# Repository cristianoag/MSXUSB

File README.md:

# MSX-USB
## Some history
In the 80's the MSX standard was created by Kazuhiko Nishi. He envisioned a simple yet powerful home computer based on standard hardware, software (BIOS/MSX DOS) and connectivity. From 1983 to 1990 manufacturers, like Philips, Sony, Yamaha, Sharp, Canon and many more, made computers according to this standard.

Because of the fact that extensibility was part of the standard people could design cartridges that would add synthesizer sound, memory, modems, rom-based games, or combinations of the above.

Cartridges were connected via a standard 50pin connector that remained the same accross 4 generations of MSX (1/2/2+/TurboR). BIOS and MSX-DOS were designed in a way to discover these via rom-based drivers, software hooks, extended bios.

Standardisation offers a big advantage because everything that adheres to the standard can connect to it.

## USB
USB was designed in the 90's to do something similar. To standardize the connection of peripherals to personal computers, both to communicate with and to supply electric power. It has now largely replaced interfaces such as serial ports and parallel ports, and has become commonplace on a wide range of devices. Like USB flash drives, keyboards, mice, wifi, serial, camera's, etc.

What if the MSX would have an USB connection? And if the BIOS/MSX DOS would automatically recognize devices connected to it?

## Meet MSX-USB
Inspired by the work of Xavirompe and his [RookieDrive](http://rookiedrive.com/en/) S0urceror set out to do build an open source project that would add USB to the MSX. The project is called MSX-USB and is hosted on GitHub. 

The project had contributions of many people in the MSX community. With people contributing to improve the hardware, firmware, drivers, and documentation.

On this GitHub page you can find:
* Schematics (KiCAD), that interfaces a cheap USB CH376s board to the MSX cartridge port.
* Drivers, currently Flash drives on Nextor and HID keyboards are supported.
* Debugging tools, to connect a test board to your PC/MAC and assist in debugging.

## Hardware

This project connects the CH376s board you can find on eBay or AliExpress for around 4 USD to the MSX.  The CH376s board is a USB host controller that can handle USB devices. The board is connected to the MSX cartridge port and is controlled by a CPLD. The CPLD is programmed to handle the MSX bus protocol and to interface with the CH376s board.

Circuitry is added to correctly handle the _BUSDIR signal. Make sure you select parallel by setting the jumper on the CH376s board correctly.

The CH376s board is accessible via ports 10h and 11h on the MSX, where port 11h serves as the command port and port 10h as the data port. 

Programming details for the CH376s can be found in various online resources:
* [CH376s Datasheet](https://www.mpja.com/download/ch376ds1.pdf)
* [Arduino Basics: CH376s USB Read/Write Module](https://arduinobasics.blogspot.com/2015/05/ch376s-usb-readwrite-module.html)

Most information is available on how to use the higher-order API for flash drives. 

If you want to use other USB devices you have to go low-level. As it turns out Konamiman already did some work there and after some researching I got USB HID Keyboards, Ethernet, Serial working as well. Check out my source-code or these great pages for more information:

* http://www.usbmadesimple.co.uk/index.html
* https://www.beyondlogic.org/usbnutshell/usb1.shtml

### PCB

If you prefer using PLCC versions of the CPLD and flash memory chips, it is recommended to use the v4 PCB by @cristianoag. This version fits into a Konami-style cartridge case and includes a switch to toggle between two ROM images. Be sure to use the rev4 CPLD code to enable this functionality. You can find the Gerber files and CPLD code for v4 at these links: [Gerber Files](hardware/v4/kicad-cpld-rev4/production) and [CPLD Code](hardware/v4/quartus-rev4).

If you’re comfortable with SMD soldering and want to avoid the challenges of sourcing 7064SLC without JTAG locks, use the v5 CPLD code and PCBs instead (also created by @cristianoag). The files for these are available at: [CPLD Code](hardware/v5/cpld) and [PCB Files](hardware/v5/kicad). The v5 CPLD verilog code also includes support to the additional 20h and 21h ports so enabling the use of new drivers that were developed for those ports by Konamiman.

Please note that for v5 there are two folders for the PCBs because there are different types of CH376 modules available. Depending on the module you have, you’ll need to use a specific version of the PCB. Compare the signals of your module with those on the PCBs to ensure you select the correct one.

**Very important:** The MSX-USB project requires modules with the CH376S firmware with at least version 0x43 (Version 3). If you have a CH376 module with a CH376S chip with versions 0x41 or 0x42 the drivers will not work. You can check the version of the firmware by issuing a CMD_GET_IC_VER command to the CH376S chip. Also some of the drivers display the version of the CH376S firmware when they are loaded.

## BIOS and Drivers

The project has several bios and drivers that have been developed. You can use a flash programmer or the MSX itself to flash the bios options to the flash chip on the cartridge. To do that use the flash.com tool that is available in the software folder. 

The flash.com command has the following syntax:

```
flash.com <filename>.rom
```

The [flash.com tool](software/flash/dist/flash.com) supports AMC_A29040B (AMIC A29040B), AMD_AM29F040, AMD_AM29F010 and SST_SST39SF040 chips. It detects the chip and selects the appropriate identification, erase and programming commands. Other chips require an external flash programmer.

Use `flash.com /S1 <filename>.rom` (or `/S0`, `/S2`, `/S3`) to select a primary slot instead of scanning all four slots. The selected slot is still checked for a supported chip before erasing. The tool erases the entire flash chip, not just the space occupied by the ROM file.

SST39SF040 commands use flash addresses `0x5555` and `0x2AAA`, rather than the shorter AMD/AMIC unlock addresses. The tool maps dedicated 8 KB command banks and temporarily replaces page 2 RAM while issuing SST commands, restoring RAM before accessing the file buffer or DOS. SST detection requires the stack to be in page 3, with at least 256 bytes available above `0xC000`. This requires the MSX-USB mapper's `5x00`/`7x00`/`9x00` bank-register decoding, as implemented by the v3, v4 and v5 CPLD sources. On v4, select the first ROM bank with the hardware switch so flash address zero is accessible for SST identification.

The host-side flash regression tests can be run with `make -C software/flash test` (Node.js and a C++17 `g++` compiler are required; `CXX` can select another compatible compiler). They exercise the actual C protocol and command-line code against a simulated flash chip and cartridge mapper; they do not replace testing on physical hardware. SST command and polling behavior follows the [Microchip datasheet](https://ww1.microchip.com/downloads/aemDocuments/documents/MPD/ProductDocuments/DataSheets/SST39SF010A-SST39SF020A-SST39SF040-Data-Sheet-DS20005022.pdf).

### USB Host BIOS (USBHOST.ROM)

S0urceror wrote a UNAPI USB specification and implemented the Usb Host driver according to it. The next version of this Host driver will also implement the Usb Hub specification and enumerate and initialise all devices connected.

* **USB HID Keyboard Driver** The Usb Keyboard driver is a program that connects to Unapi Usb driver and hooks itself to H.CHGE. From that moment on it replaces your trusted MSX keyboard by a shiny new USB Keyboard. Or a wireless one if you have inserted the appropriate Logitech receiver.

* **USB CDC ECM Ethernet Driver** The USB CDC ECM Ethernet driver is finished. It uses the Unapi USB and conforms to the Unapi Ethernet standard. Internestor Lite can now connect and use your USB Ethernet device. Please note that currently we only support USB CDC ECM. Make sure your Ethernet device supports this. All USB Ethernet devices built around the **RTL8153** chipset support USB CDC ECM. They usually cost around 20 euro.

### USB Storage NEXT (USBNEXT.ROM)

This is a firmware developed in C that implements a menu that is capable to mount DSK files or boot the computer from a connected USB stick. It also is a Nextor driver that allows you to use the USB stick as a hard disk. 

You can choose between (1) to initialize via floppy disk, (2) to initialize via USB stick, or use letters correspondent to files and folders located on the root of the USB stick connected to the cartridge to navigate and mount DSK files.

This BIOS allows mounting DSK files that are bigger than 720KB, respecting the limitations imposed by the Nextor OS.

### Konamiman USB FDD Firmware (USBFDD.ROM)

Konamiman developed a BIOS that allows you to mount DSK 360K/720K images stored on a USB floppy drive and use them as if they were real floppy disks. This version also allows you to boot the computer from a connected USB floppy drive compatible with the UFI standard.

You can check the [Konamiman's Floppy Disk Controller ROM](https://github.com/Konamiman/RookieDrive-FDD-ROM) GitHub repository for more information. He also provides a full manual page describing how to use the BIOS in the [Disk Image Mode](https://github.com/Konamiman/RookieDrive-FDD-ROM/blob/master/DISK_IMAGE_MODE.md).

@cristianoag adapted the original BIOS to work with the MSX-USB project. You can find the adapted version in the [MsxUSBFDD](/drivers/MsxUSBFDD) folder. 

## Installation instructions
Check [this page](INSTALL.md) for installation instructions and links to the various binaries that have been developed.

## Build your own (DIY)
Check [this page](DIY.md) for information on how to make the PCB, program the CPLD device, flash the ROM, etc.

## Collaboration
Interested in contributing to the MSX-USB project? Whether you want to develop drivers for additional devices or assist in other areas, your help is welcome. Clone the repository and start contributing by filing issues, submitting pull requests, or sharing your ideas.

## License

This work is licensed under a [Creative Commons Attribution-NonCommercial-ShareAlike 4.0 International License](http://creativecommons.org/licenses/by-nc-sa/4.0/).

* If you remix, transform, or build upon the material, you must distribute your contributions under the same license as the original.
* You may not use the material for commercial purposes.
* You must give appropriate credit, provide a link to the license, and indicate if changes were made. You may do so in any reasonable manner, but not in any way that suggests the licensor endorses you or your use.

**ATTENTION**

This project was made for the retro community and not for commercial purposes. So only retro hardware forums and individual people can build this project.

THE SALE OF ANY PART OF THIS PROJECT WITHOUT EXPRESS AUTHORIZATION IS PROHIBITED!

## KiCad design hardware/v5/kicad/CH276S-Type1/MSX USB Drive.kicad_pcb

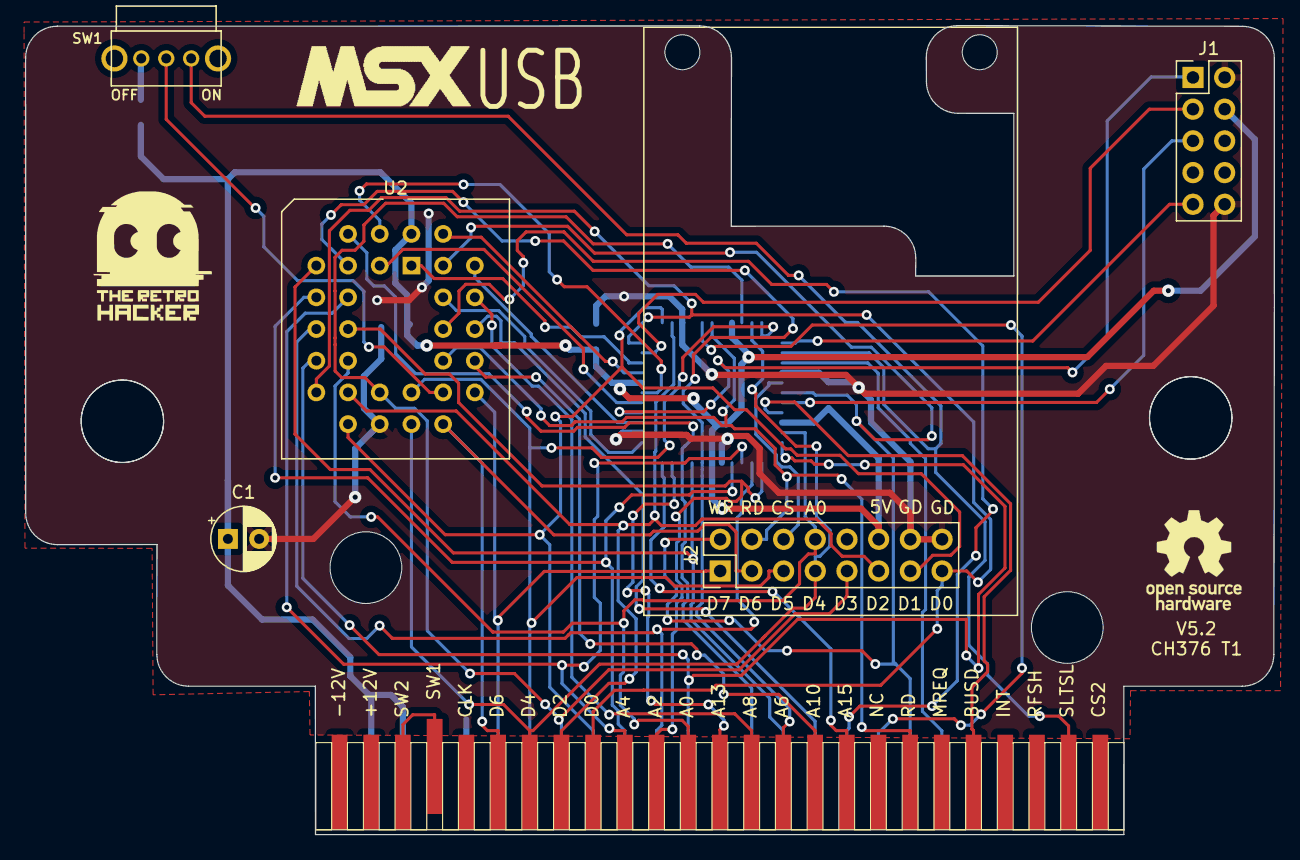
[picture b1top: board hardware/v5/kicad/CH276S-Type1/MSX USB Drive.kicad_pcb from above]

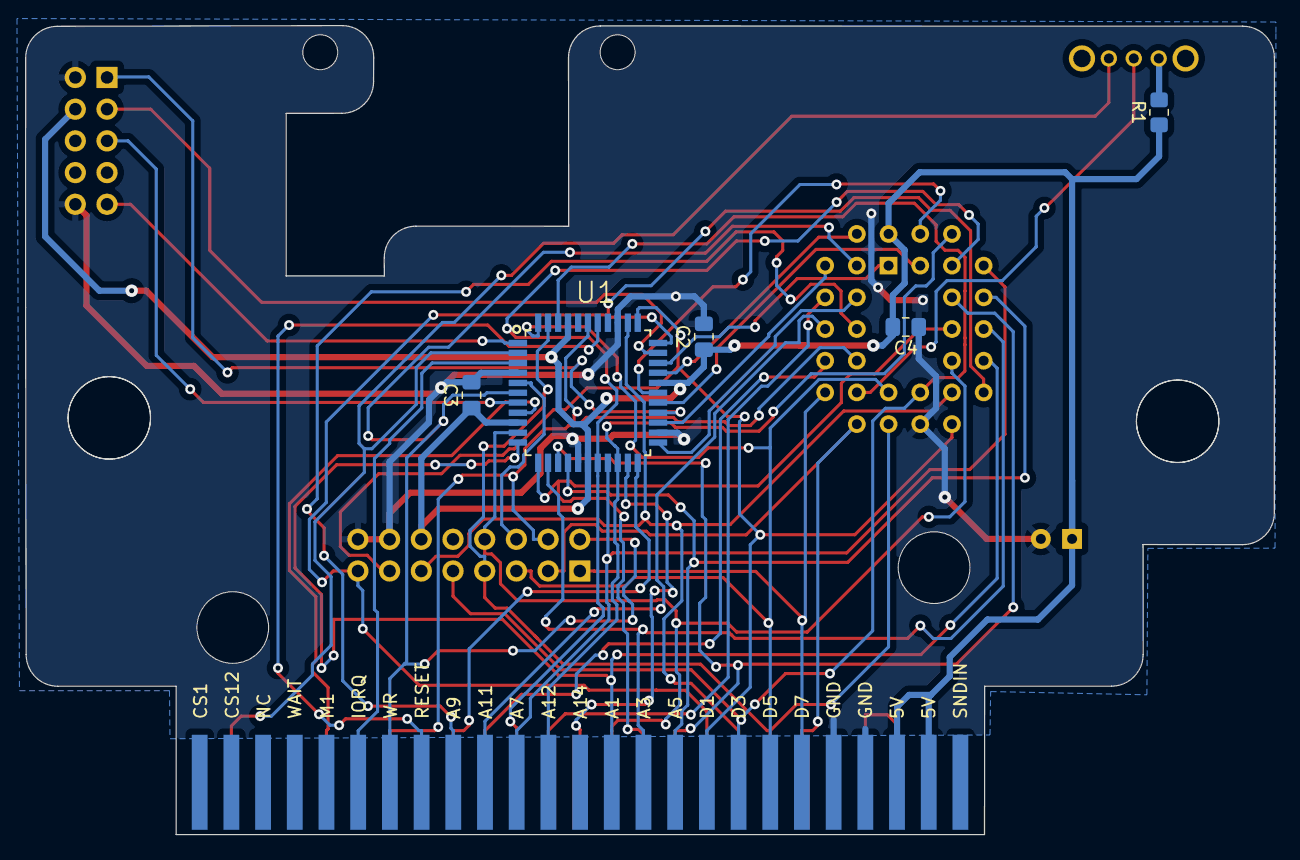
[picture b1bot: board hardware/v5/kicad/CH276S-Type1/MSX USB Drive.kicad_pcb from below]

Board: 2 copper layers, 100.1 x 64.8 mm, 12 parts (5 on the bottom side), 45 nets.

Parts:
C1: 100 uF; CP_Radial_D5.0mm_P2.50mm
C2, C3, C4: 0.1 uF; C_0805_2012Metric_Pad1.18x1.45mm_HandSolder
EDG1: MSX_CON; msx-con-MSXCART
J1: AVR-JTAG-10; PinHeader_2x05_P2.54mm_Vertical
J2: Conn_02x08_Odd_Even; PinHeader_2x08_P2.54mm_Vertical
LOGO_MSX: LOGO_MSX
R1: 10KR; R_0805_2012Metric_Pad1.20x1.40mm_HandSolder
SW1: SK12D07VG4
U1: EPM7064STC44-7; QFP80P1200X1200X120-44N
U2: SST39SF040; PLCC-32_THT-Socket

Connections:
A0: EDG1.A0, J2.8, U1.10 (IO_7), U2.12 (A0)
A1: EDG1.A1, U1.11 (IO_8), U2.11 (A1)
A2: EDG1.A2, U1.12 (IO_9), U2.10 (A2)
A3: EDG1.A3, U1.13 (IO_10), U2.9 (A3)
A4: EDG1.A4, U1.14 (IO_11), U2.8 (A4)
A5: EDG1.A5, U1.15 (IO_12), U2.7 (A5)
A6: EDG1.A6, U1.18 (IO_13), U2.6 (A6)
A7: EDG1.A7, U1.19 (IO_14), U2.5 (A7)
A8: EDG1.A8, U2.27 (A8)
A9: EDG1.A9, U2.26 (A9)
A10: EDG1.A10, U2.23 (A10)
A11: EDG1.A11, U2.25 (A11)
A12: EDG1.A12, U1.20 (IO_15), U2.4 (A12)
A13: EDG1.A13, U1.21 (IO_16)
A15: EDG1.A15, U1.22 (IO_17)
BUSDIR_: EDG1./BUSDIR (~BUSDIR), U1.8 (IO_6)
CS_: J2.6, U1.5 (IO_4)
D0: EDG1.D0, J2.15, U1.33 (IO_24), U2.13 (D0)
D1: EDG1.D1, J2.13, U1.34 (IO_25), U2.14 (D1)
D2: EDG1.D2, J2.11, U1.35 (IO_26), U2.15 (D2)
D3: EDG1.D3, J2.9, U1.42 (IO_27), U2.17 (D3)
D4: EDG1.D4, J2.7, U1.43 (IO_28), U2.18 (D4)
D5: EDG1.D5, J2.5, U1.44 (IO), U2.19 (D5)
D6: EDG1.D6, J2.3, U2.20 (D6)
D7: EDG1.D7, J2.1, U2.21 (D7)
GND: C1.2, C2.2, C3.2, C4.1, EDG1.GND1 (GND), EDG1.GND2 (GND), J1.2 (GND), J1.10 (GND), J2.14, J2.16, U1.4 (GND_4), U1.16 (GND_2), U1.24 (GND), U1.36 (GND_3), U2.16 (GND)
IORQ_: EDG1./IORQ (~IORQ), U1.3 (IO_3)
MA13: U1.23 (IO_18), U2.28 (A13)
MA14: U1.25 (IO_19), U2.29 (A14)
MA15: U1.27 (IO_20), U2.3 (A15)
MA16: U1.28 (IO_21), U2.2 (A16)
MA17: U1.30 (IO_22), U2.30 (A17)
MA18: U1.31 (IO_23), U2.1 (A18)
unnamed: EDG1.SW1, EDG1.SW2
unnamed: R1.2, SW1.2
unnamed: SW1.COM, U2.22 (CE)
RD_: EDG1./RD (~RD), J2.4, U1.39 (INPUT/~GCLR), U2.24 (OE)
RESET_: EDG1./RESET (~RESET), U1.38 (INPUT/OE1)
SLTSL_: EDG1./SLTSL (~SLTSL), SW1.1, U1.2 (IO_2)
TCK: J1.1 (TCK), U1.26 (IO/TCK)
TDI: J1.9 (TDI), U1.1 (IO/TDI)
TDO: J1.3 (TDO), U1.32 (IO/TDO)
TMS: J1.5 (TMS), U1.7 (IO/TMS)
VCC: C1.1, C2.1, C3.1, C4.2, EDG1.+5V1 (+5V), EDG1.+5V2 (+5V), J1.4 (VREF), J2.12, R1.1, U1.9 (VCCINT), U1.17 (VCCINT_2), U1.29 (VCCINT_3), U1.41 (VCCINT_4), U2.32 (VCC)
WR_: EDG1./WR (~WR), J2.2, U1.6 (IO_5), U2.31 (PGM)

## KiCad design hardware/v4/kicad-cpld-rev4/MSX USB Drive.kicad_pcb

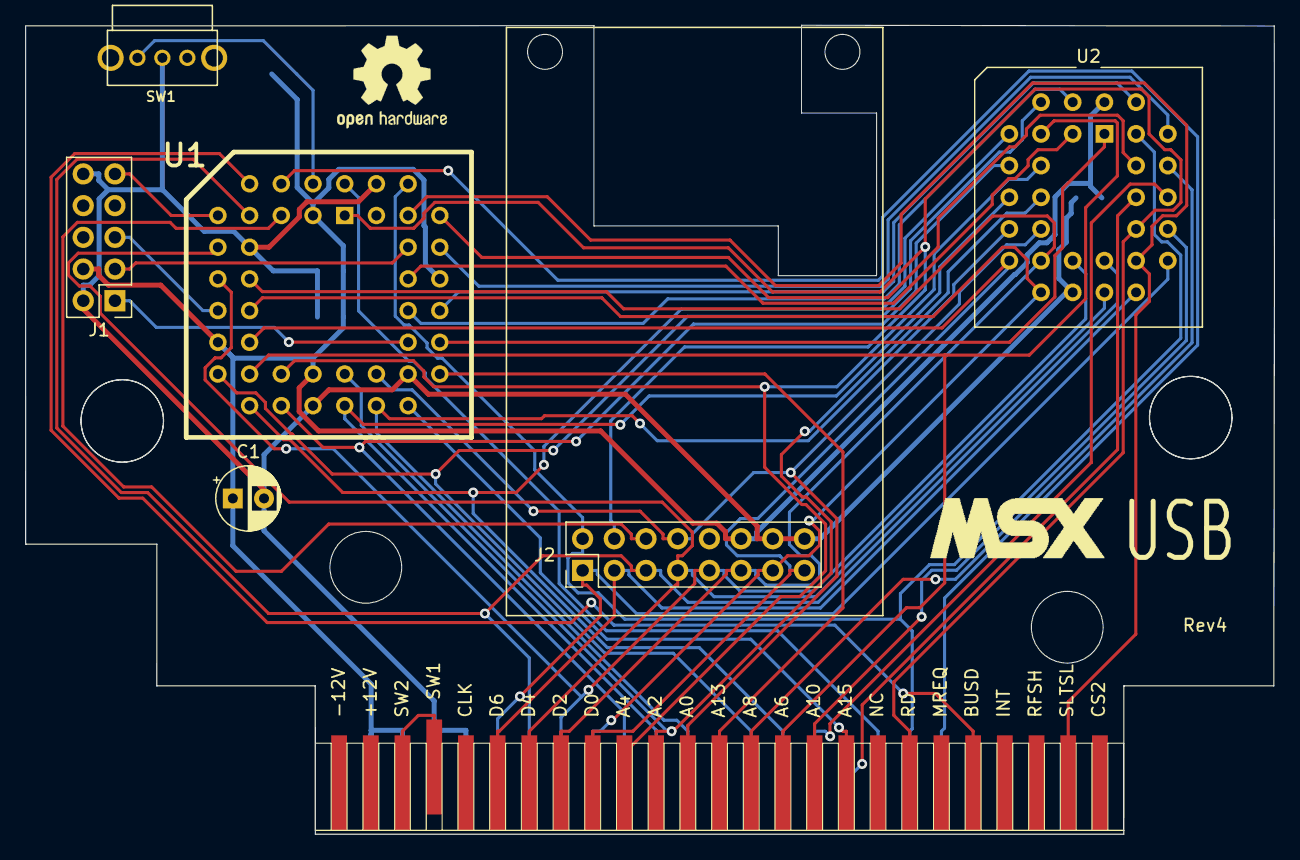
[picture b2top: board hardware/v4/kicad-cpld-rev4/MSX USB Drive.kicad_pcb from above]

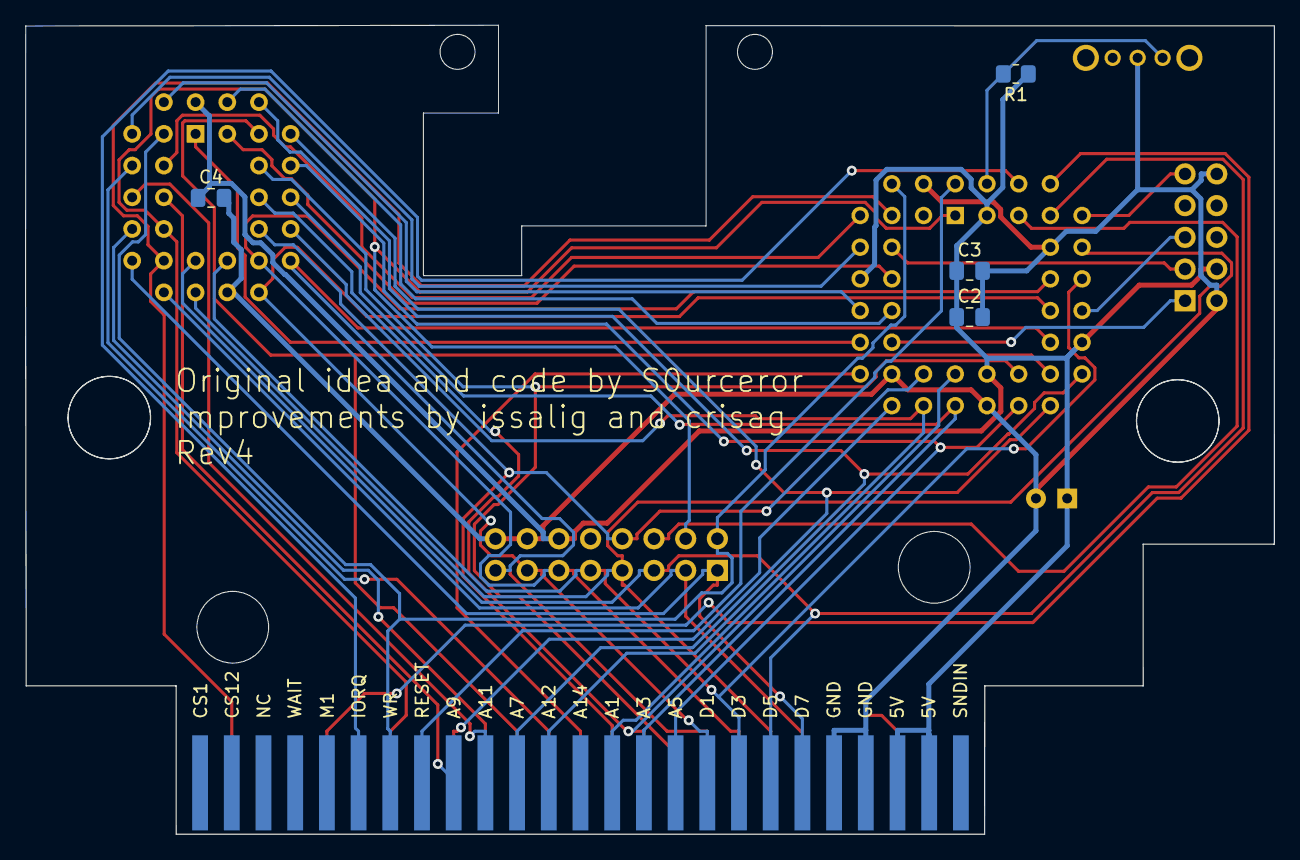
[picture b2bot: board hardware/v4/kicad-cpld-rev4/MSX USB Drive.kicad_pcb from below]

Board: 2 copper layers, 100.1 x 64.8 mm, 12 parts (4 on the bottom side), 44 nets.

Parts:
C1: 100 uF; CP_Radial_D5.0mm_P2.50mm
C2, C3, C4: 0.1 uF; C_0805_2012Metric_Pad1.18x1.45mm_HandSolder
EDG1: MSX_CON; msx-con-MSXCART
J1: AVR-JTAG-10; PinHeader_2x05_P2.54mm_Vertical
J2: Conn_02x08_Odd_Even; PinHeader_2x08_P2.54mm_Vertical
LOGO_MSX: LOGO_MSX
R1: 4K7; R_0805_2012Metric_Pad1.20x1.40mm_HandSolder
SW1: SK12D07VG4
U1: EPM7032_7064; PLCC44
U2: AM29f040; PLCC-32_THT-Socket

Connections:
A0: EDG1.A0, J2.8, U1.27 (I/O), U2.12 (A0)
A1: EDG1.A1, U1.26 (I/O), U2.11 (A1)
A2: EDG1.A2, U1.25 (I/O), U2.10 (A2)
A3: EDG1.A3, U1.24 (I/O), U2.9 (A3)
A4: EDG1.A4, U1.21 (I/O), U2.8 (A4)
A5: EDG1.A5, U1.20 (I/O), U2.7 (A5)
A6: EDG1.A6, U1.19 (I/O), U2.6 (A6)
A7: EDG1.A7, U1.18 (I/O), U2.5 (A7)
A8: EDG1.A8, U2.27 (A8)
A9: EDG1.A9, U2.26 (A9)
A10: EDG1.A10, U2.23 (A10)
A11: EDG1.A11, U2.25 (A11)
A12: EDG1.A12, U1.17 (I/O), U2.4 (A12)
A13: EDG1.A13, U1.29 (I/O)
A15: EDG1.A15, U1.28 (I/O)
BUSDIR_: EDG1./BUSDIR (~BUSDIR), U1.6 (I/O)
CS_: J2.6, U1.5 (I/O)
D0: EDG1.D0, J2.15, U1.16 (I/O), U2.13 (D0)
D1: EDG1.D1, J2.13, U1.14 (I/O), U2.14 (D1)
D2: EDG1.D2, J2.11, U1.12 (I/O), U2.15 (D2)
D3: EDG1.D3, J2.9, U1.11 (I/O), U2.17 (D3)
D4: EDG1.D4, J2.7, U1.9 (I/O), U2.18 (D4)
D5: EDG1.D5, J2.5, U1.8 (I/O), U2.19 (D5)
D6: EDG1.D6, J2.3, U2.20 (D6)
D7: EDG1.D7, J2.1, U2.21 (D7)
GND: C1.2, C2.2, C3.2, C4.2, EDG1.GND1 (GND), EDG1.GND2 (GND), J1.2 (GND), J1.10 (GND), J2.14, J2.16, SW1.COM, U1.10 (GND), U1.22 (GND), U1.30 (GND), U1.42 (GND), U2.16 (GND)
IORQ_: EDG1./IORQ (~IORQ), U1.4 (I/O)
MA13: U1.39 (I/O), U2.28 (A13)
MA14: U1.37 (I/O), U2.29 (A14)
MA15: U1.36 (I/O), U2.3 (A15)
MA16: U1.34 (I/O), U2.2 (A16)
MA17: U1.33 (I/O), U2.30 (A17)
MA18: U1.31 (I/O), U2.1 (A18)
RD_: EDG1./RD (~RD), J2.4, U1.1 (GCLRn), U2.24 (OE)
RESET_: EDG1./RESET (~RESET), U1.44 (OE1)
SEL_F1F2: R1.2, SW1.2, U1.2 (I/O|OE2|GCLK2)
SLTSL_: EDG1./SLTSL (~SLTSL), U1.41 (I/O), U2.22 (CE)
SW1: EDG1.SW1, EDG1.SW2
TCK: J1.1 (TCK), U1.32 (TCK)
TDI: J1.9 (TDI), U1.7 (TDI)
TDO: J1.3 (TDO), U1.38 (TDO)
TMS: J1.5 (TMS), U1.13 (TMS)
VCC: C1.1, C2.1, C3.1, C4.1, EDG1.+5V1 (+5V), EDG1.+5V2 (+5V), J1.4 (VREF), J2.12, R1.1, U1.3 (VCC), U1.15 (VCC), U1.23 (VCC), U1.35 (VCC), U2.32 (VCC)
WR_: EDG1./WR (~WR), J2.2, U1.40 (I/O), U2.31 (PGM)

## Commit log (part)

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2025-03-21 init on private
2025-03-21 remaining
